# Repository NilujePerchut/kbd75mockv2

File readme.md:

# KBD75mockV2

An open-source KBD75V2 alternative PCB with the following features:
- STM32F103 microcontroller
- Per-Key RGB backlight (SK6812MINI-E)
- 16 RGB backlight LEDs (compatible with offical foam hole location)
- USB-C connector
- AINSI & ISO layouts
- Alternate layout for spacebar right side keys
- Mechanicaly compatible with the KBDFans KBD75V2 case
- Also compatible with the YMDK84 case (tested with acrylic case)
- QMK compatible (see [qmk firmware support](https://github.com/NilujePerchut/qmk_firmware/tree/kbd75mockv2))
- JLCPCB friendly workflow:
    - Complies with JLCPCB design rules
    - Uses component available at JLCPCB SMT part

## Disclamers
I am not affiliated in any way with the KBDFans corporation. This is NOT a KBDFans product.

This design comes with no warranty at all. See LICENSE file for more details.

# Status
Rev A0 prototype assembled and functionnal.
See Bug section below for more details.

## RevA0 Bugs
- Some fixing holes are not aligned with official KBD75V2 case inserts.
- Missing one RGB backlight led on each lateral side. This creates a hole in the surrounding ring.

## Usage

Be sure to understand the [Status](#status) and [Bugs](reva0-bugs) sections before investing money in such project.

```
git clone --recurse-submodules https://github.com/NilujePerchut/kbd75mockv2
```
_Note:_ This project uses [skidl](https://github.com/devbisme/skidl) to produce a netlist instead of using a regular schematics editor. It also relies on some automatic routing via python scripts for repetitive placement and routing tasks. The PCB is then completed by hand using kicad's pcbnew.

### PCB manufaturing & assembly
Open the [Routed PCB](hard/pcb/final_pcb/kbd75mock_v2_routed.kicad_pcb) with kicad and generate the GERBER files.

All relevant footprints have a _JLCC_ field with JLCPCB SMT command code. This can be used to generate JLCPCB assembly request.

### Configuration
If you need the per-key RGB backlight feature, make a solder joint between pins 1 and 2 of P3.

### QMK firmware

All related files are located in the [qmk_firmware](qmk_firmware) directory.

The compilation and flashing steps use the convenient `qmk` cli tool provided by qmk_firmware. See [QMK cli](https://docs.qmk.fm/#/cli) for more details. 

## Bootloader installation
This board uses the standard stm32duino bootloader. The SWD P2 connector to flash it using your prefered method (tested with an STLINKV2 clone).

## Compilation
```
cd qmk_firmware
qmk compile -km default -kb kbd75mockv2
```

## Flashing
```
qmk flash -km default -kb kbd75mockv2
```

_WARNING_: Default RGB MATRIX (per key LEDs) max brightness is set to 0x100. This value causes the whole PCB (including RGB backlight) to drain around 400mA on the USB bus.This represents more than 2W of power consumption and clearly heats the whole structure. You might want to lower this value to lower heat dissipation.

## RevA1 TODO
- [ ] Rework PCB routing to enhance performances
- [ ] Fix location of mechanical fixing holes
- [ ] Move backlight RGB LEDs to be compliant with official foam
- [ ] Add one more RGB backlight LED one each lateral side
- [ ] (if possible) Add split backspace option
- [ ] (if possible) Add alternate tab key option
- [ ] (if possible) Add split spacebar option

## Galerie

## Credits & Thanks
- Benoit, Tor-Rolf, Damien & Pascale for the precious help
- [KBDFans](https://kbdfans.com/)
- [QMK](https://qmk.fm/)
- [SKIDL](https://github.com/devbisme/skidl)
- [Kicad]

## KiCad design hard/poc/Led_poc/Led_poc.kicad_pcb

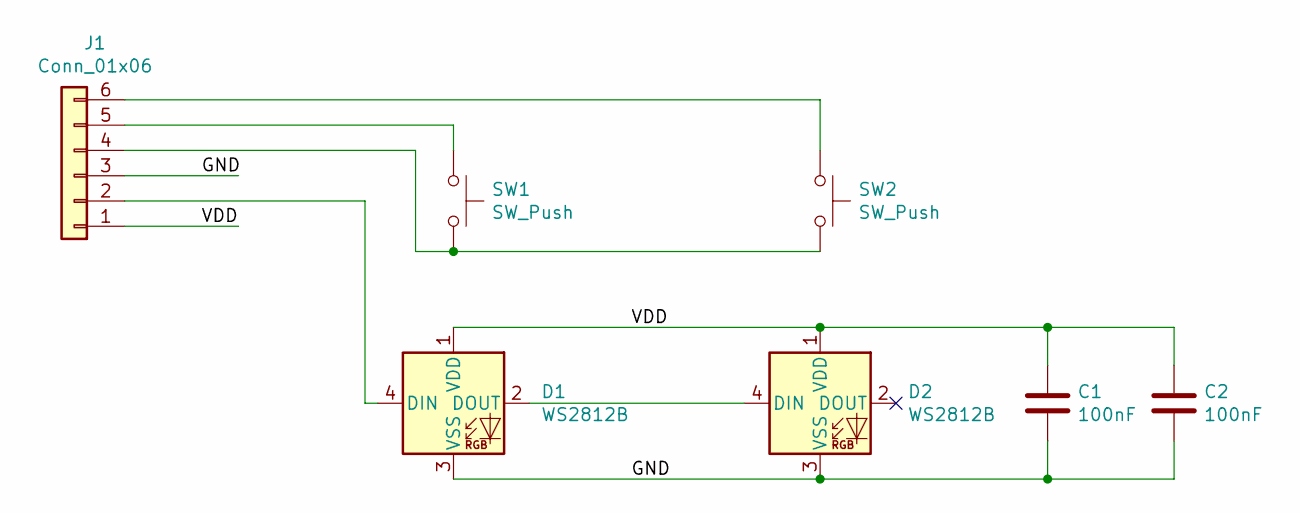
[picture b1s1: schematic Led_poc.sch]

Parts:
C1, C2: 100nF; C_0201_0603Metric_Pad0.64x0.40mm_HandSolder
D1, D2: WS2812B; SK6812
J1: Conn_01x06; PinHeader_1x06_P2.54mm_Vertical
SW1, SW2: SW_Push; SW_Cherry_MX_1.00u_PCB

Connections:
/GND: C1.2, C2.2, D1.3 (VSS), D2.3 (VSS), J1.3
/VDD: C1.1, C2.1, D1.1 (VDD), D2.1 (VDD), J1.1
unnamed: D1.2 (DOUT), D2.4 (DIN)
unnamed: D1.4 (DIN), J1.2
unnamed: J1.4, SW1.2, SW2.2
unnamed: J1.5, SW1.1
unnamed: J1.6, SW2.1

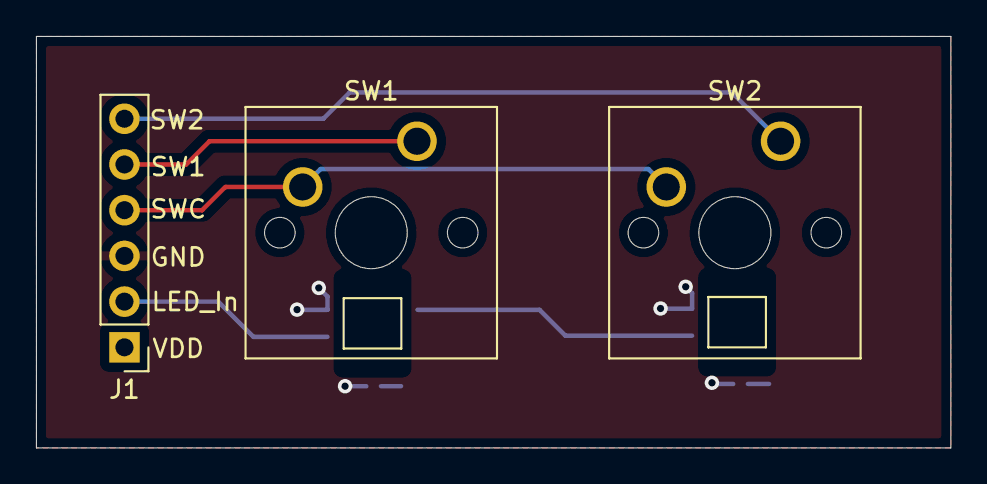
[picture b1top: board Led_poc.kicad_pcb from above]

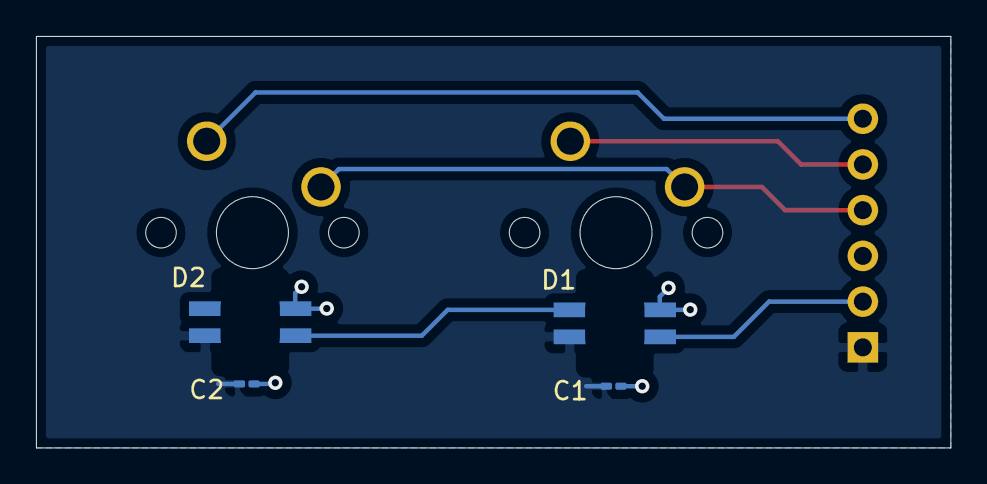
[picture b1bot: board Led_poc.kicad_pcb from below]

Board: 2 copper layers, 50.8 x 22.9 mm, 7 parts (4 on the bottom side), 7 nets.

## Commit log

2021-07-16 Switches to more classical infra
2021-07-18 Adds gitignore
2021-07-18 Add usb_iface +needed infra
2021-07-22 Fix USB dict indexing
2021-07-23 STM32 first version
2021-08-01 Leds
2021-08-01 Refactor leds to include bakclight
2021-08-01 Add A SIL4 for external USB connection
2021-08-01 Mechanicals, work in progress
2021-08-01 Regulator + unit test
2021-08-01 Update Makefile
2021-08-01 STM32 + unit test
2021-08-01 Key matrix + unit tests
2021-08-01 Updates TODO with post schematics tasks
2021-08-01 Setup a todo_file
2021-08-01 Add global gitignore
2021-08-01 Adds a setenv file
    Just source the file and its ok
2021-08-03 First placement POC
2021-08-06 Implements uniq key in json
2021-08-06 Update placement
2021-08-06 Remove split spacebar option
2021-08-06 Move per key led chain start at bottom left
2021-08-06 Switch backlight LEDs to 5050 WS2812B
2021-08-08 Reverser Stab holes for space bar
2021-08-08 Update Mech with fix holes and update final keyboard
2021-08-08 Add documentation about mounting types
2021-08-08 Move/Rotate the LED designator to avoid switch hole
2021-08-08 Allow LED chain alternate command
2021-08-09 Place Backlight LEDs
2021-08-14 Fix typo
2021-08-14 Add number of row info from KLE parsing
2021-08-14 Add decoupling capas
2021-08-19 Rework USB interface
2021-08-19 Use dedicated ainsi backslash footprint with enlarged #1 pad
2021-08-23 Rework doc dir structure
2021-08-23 Add manual placement step
2021-08-23 Add route with automatic Edge.Cuts
2021-08-23 Place Keyboard fixes
2021-08-23 Update todo
2021-08-23 Add GPLV3 license file
2021-08-23 First manual placement
2021-08-23 Add tmp dir to .gitignore
2021-08-30 Add routing script with edge cut
2021-08-31 Add diode anonde routing
2021-09-01 Add GND and V5V planes
2021-09-05 Place via on LEDs GND
2021-09-05 Route LED links
2021-09-06 Rebuild zones at the end of routing
2021-09-11 Add YMDK case + placement
2021-09-11 Defines Power netclass
2021-09-14 Set Key values not visible (already in overlay)
2021-09-14 Invert USB_P & USB_N
2021-09-14 Place USB interface
2021-09-16 Adjust LEDs GND vias distance
2021-09-16 Suppress 45° in LED chain routing
2021-10-01 Fix voltage for general bypass capacitor
    3.3V to 5V
2021-10-01 Add JLCPCB code for backlight RGB diodes
2021-10-01 Use a bigger Sakura !
2021-10-01 Adjust via diameter
2021-10-01 Change power Ferrite
2021-10-01 Update STM32 pinout to ease the routing process
2021-10-01 Add jlcpcb assembly makefile target
2021-10-01 Update datasheets
2021-10-01 Add final PCB
2021-10-03 Add kicad_libs from submodule
2021-12-09 Add qmk_firmware submodule
2021-12-09 Update validation todo
2021-12-10 Add readme
